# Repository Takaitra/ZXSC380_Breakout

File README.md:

# ZXSC380 Breakout Board

This is a breadboard-friendly breakout board for the ZXSC380 LED driver. This repository contains the Eagle design files. You will also need to install the [Takaitra Eagle library](https://github.com/Takaitra/Takaitra-Eagle-Libraries). This breakout board is used in my [tutorial on designing and building an SMD breakout board](https://www.takaitra.com/design-build-smd-breakout-board/).

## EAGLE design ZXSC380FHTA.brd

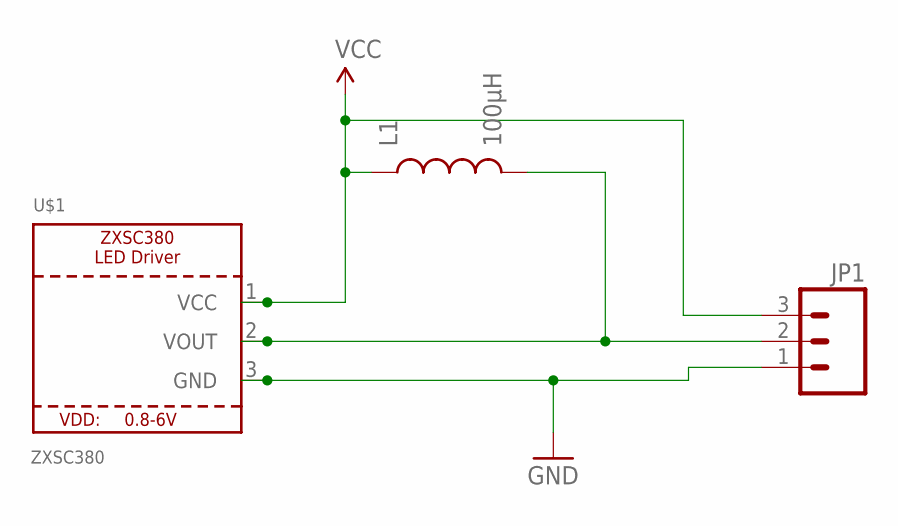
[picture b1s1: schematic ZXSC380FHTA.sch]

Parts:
JP1: M03PTH; 1X03
L1: 100µH; 0805
U$1: ZXSC380; SOT-23

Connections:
GND: JP1.1, U$1.3 (GND)
VCC: JP1.3, L1.1, U$1.1 (VCC)
VOUT: JP1.2, L1.2, U$1.2 (VOUT)

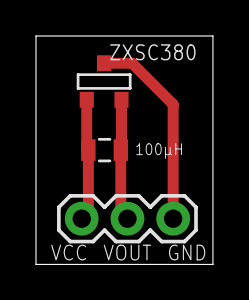
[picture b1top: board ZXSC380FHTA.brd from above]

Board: 2 copper layers, 9.8 x 12.7 mm, 3 parts (0 on the bottom side), 3 nets.

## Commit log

2018-05-22 Add design files and update README

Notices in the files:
parts and their libraries:
SparkFun-Connectors: Licensing: Creative Commons ShareAlike 4.0 International - https://creativecommons.org/licenses/by-sa/4.0
